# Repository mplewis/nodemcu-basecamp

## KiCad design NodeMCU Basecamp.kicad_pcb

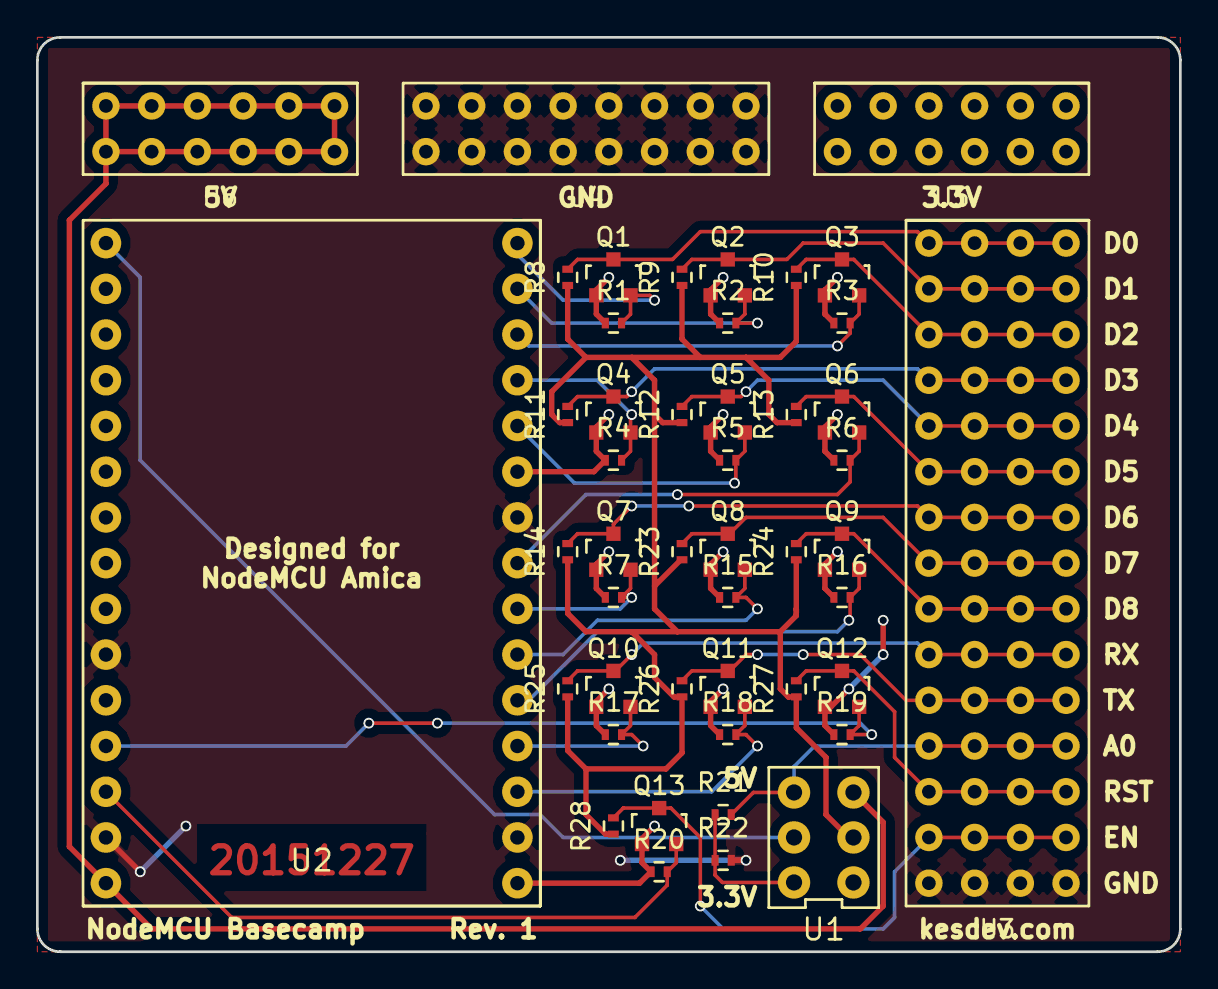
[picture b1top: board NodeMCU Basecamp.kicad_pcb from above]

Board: 2 copper layers, 63.5 x 50.8 mm, 47 parts (0 on the bottom side), 33 nets.

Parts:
Q1, Q2, Q3, Q4, Q5, Q6, Q7, Q8, Q9, Q10, Q11, Q12, Q13: BSS138; SOT-23
R1, R2, R3, R4, R5, R6, R7, R8, R9, R10, R11, R12, R13, R14, R15, R16, R17, R18, R19, R20, R23, R24, R25, R26, R27, R28: 10K; R_0402
R21: 33K; R_0402
R22: 68K; R_0402
U1: JS202011CQN
U2: NODEMCU_AMICA
U3: DEV_PINS; HEADER_STRIP_15X4
U4: GND_BUS; HEADER_BUS_4X8
U5: 3V3_BUS; HEADER_BUS_4X6
U6: 5V_BUS; HEADER_BUS_4X6

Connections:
3V3: Q1.1, Q2.1, Q3.1, Q4.1, Q5.1, Q6.1, Q7.1, Q8.1, Q9.1, Q10.1, Q11.1, Q12.1, Q13.1, R1.1, R2.1, R3.1, R4.1, R5.1, R6.1, R7.1, R15.1, R16.1, R17.1, R18.1, R19.1, R20.1, U1.1, U2.11, U2.16, U2.25, U5.1
5V: U1.3, U2.15, U6.1
A0_LV: U1.5, U2.1
A0_STEPDOWN: R21.1, R22.1, U1.6
A0_XV: R21.2, U1.4, U3.12
D0_LV: Q1.2, R1.2, U2.30
D0_XV: Q1.3, R8.2, U3.1
D1_LV: Q2.2, R2.2, U2.29
D1_XV: Q2.3, R9.2, U3.2
D2_LV: Q3.2, R3.2, U2.28
D2_XV: Q3.3, R10.2, U3.3
D3_LV: Q4.2, R4.2, U2.27
D3_XV: Q4.3, R11.2, U3.4
D4_LV: Q5.2, R5.2, U2.26
D4_XV: Q5.3, R12.2, U3.5
D5_LV: Q6.2, R6.2, U2.23
D5_XV: Q6.3, R13.2, U3.6
D6_LV: Q7.2, R7.2, U2.22
D6_XV: Q7.3, R14.2, U3.7
D7_LV: Q8.2, R15.2, U2.21
D7_XV: Q8.3, R23.2, U3.8
D8_LV: Q9.2, R16.2, U2.20
D8_XV: Q9.3, R24.2, U3.9
EN_LV: Q12.2, R19.2, U2.12
EN_XV: Q12.3, R27.2, U3.13
Earth: R22.2, U2.10, U2.14, U2.17, U2.24, U3.15, U4.1
OP_V: R8.1, R9.1, R10.1, R11.1, R12.1, R13.1, R14.1, R23.1, R24.1, R25.1, R26.1, R27.1, R28.1, U1.2
RST_LV: Q13.2, R20.2, U2.13
RST_XV: Q13.3, R28.2, U3.14
RX_LV: Q10.2, R17.2, U2.19
RX_XV: Q10.3, R25.2, U3.10
TX_LV: Q11.2, R18.2, U2.18
TX_XV: Q11.3, R26.2, U3.11

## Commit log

2015-12-28 git: initial commit
2015-12-28 rework: remove jumpers
2015-12-28 pcb: LT wired to dev pins
2015-12-28 pcb: wired bus dev pins and floating gnd island
2015-12-28 pcb: first draft
2015-12-28 pcb: rev 1 gerbers sent to DirtyPCBs
2016-01-19 pcb: improvements to text, fills, islands, drill sizes
